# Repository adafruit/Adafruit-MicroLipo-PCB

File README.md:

# Adafruit MicroLipo and MiniLipo Charging Boards/Backpacks

&nbsp; 
<br />
&nbsp; 
<br />
&nbsp; 
<br />

Click to purchase from the Adafruit Shop:
- [Adafruit Micro-Lipo Charger for LiPo/LiIon Batt w/MicroUSB Jack - v1](https://www.adafruit.com/product/1904)
- [Adafruit Micro Lipo - USB LiIon/LiPoly charger - v1](https://www.adafruit.com/product/1304)
- [Adafruit Mini Lipo w/Mini-B USB Jack - USB LiIon/LiPoly charger - v1](https://www.adafruit.com/product/1905)
- [Adafruit LiIon/LiPoly Backpack Add-On for Pro Trinket/ItsyBitsy](https://www.adafruit.com/product/2124)
- [Adafruit Micro-Lipo Charger for LiPoly Batt with USB Type C Jack](https://www.adafruit.com/product/4410)
- [Adafruit Micro Lipo - USB LiIon/LiPoly charger - v2](https://www.adafruit.com/product/1304)

Oh so handy, this little lipo charger is so small and easy to use you can keep it on your desk or mount it easily into any project! Simply plug it via any MicroUSB cable into a USB port and a 3.7V/4.2V lithium polymer or lithium ion rechargeable battery into the JST plug on the other end. There are two LEDs - one red and one green. While charging, the red LED is lit. When the battery is fully charged and ready for use, the green LED turns on. Seriously, it could not get more easy.

These are the PCB files for the Adafruit Mini/MicroLipo battery chargers. The 
Format is EagleCAD schematic and board layout.

### License

Adafruit invests time and resources providing this open source design, please support Adafruit and open-source hardware by purchasing products from [Adafruit](https://www.adafruit.com)!

All text above must be included in any redistribution

Designed by Limor Fried/Ladyada for Adafruit Industries.
Creative Commons Attribution/Share-Alike, all text above must be included in any redistribution. 
See license.txt for additional information.

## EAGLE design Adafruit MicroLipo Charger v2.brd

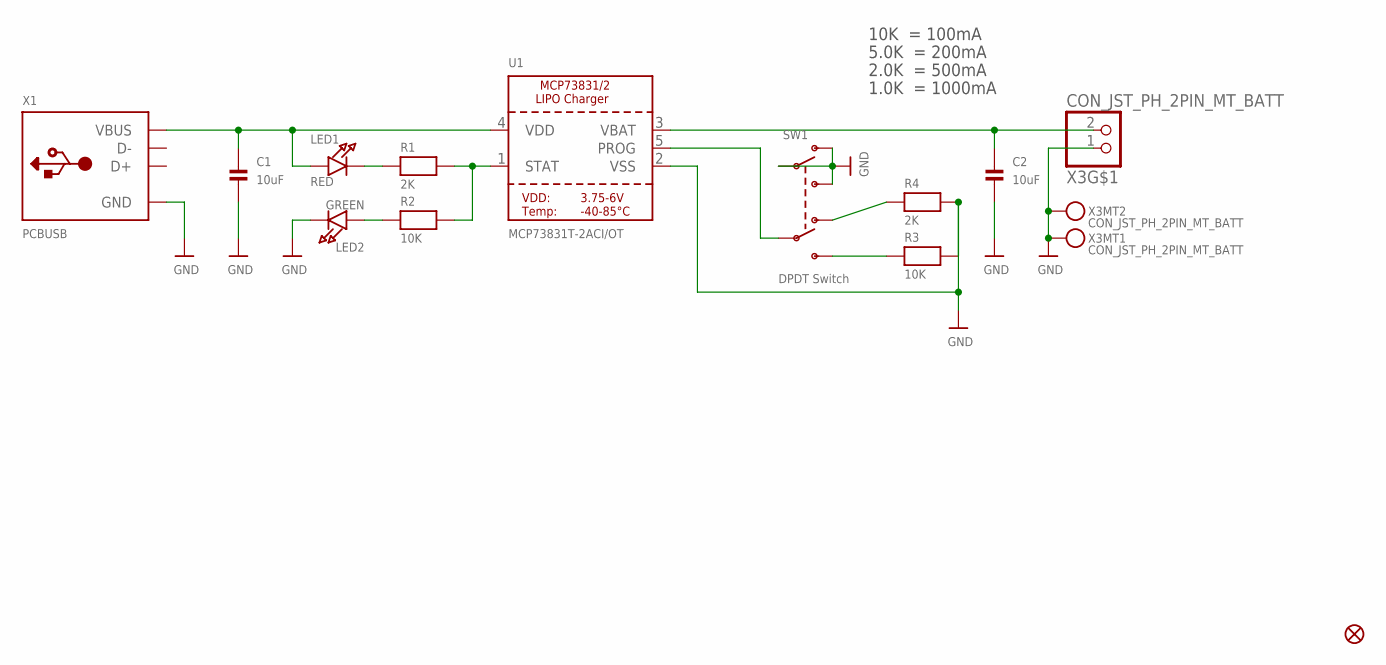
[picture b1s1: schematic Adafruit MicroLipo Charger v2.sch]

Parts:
C1, C2: 10uF; 0805-NO
FID1: FIDUCIAL_1MM
LED1: RED; CHIPLED_0603_NOOUTLINE
LED2: GREEN; CHIPLED_0603_NOOUTLINE
R1, R4: 2K; 0603-NO
R2, R3: 10K; 0603-NO
SW1: DPDT Switch; EG1390
U1: MCP73831T-2ACI/OT; SOT23-5
X1: PCBUSB; USBA_PCB
X3: CON_JST_PH_2PIN_MT_BATT; JSTPH2_BATT

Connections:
GND: C1.2, C2.2, LED2.C, R3.2, R4.2, SW1.O1, SW1.P1, SW1.S1, U1.2 (VSS), X1.GND, X3.1, X3.NC1, X3.NC2
unnamed: LED1.C, R1.1
unnamed: R1.2, R2.2, U1.1 (STAT)
unnamed: R3.1, SW1.S2
unnamed: R4.1, SW1.O2
unnamed: SW1.P2, U1.5 (PROG)
unnamed: LED2.A, R2.1
VBAT: C2.1, U1.3 (VBAT), X3.2
VDD: C1.1, LED1.A, U1.4 (VDD), X1.VCC (VBUS)

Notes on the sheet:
10K = 100mA
5.0K = 200mA
2.0K = 500mA
1.0K = 1000mA

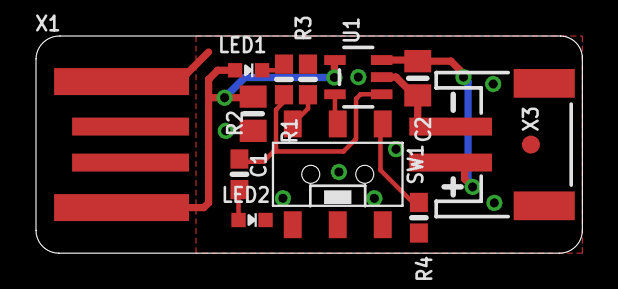
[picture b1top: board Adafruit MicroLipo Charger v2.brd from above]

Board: 2 copper layers, 30.4 x 12.1 mm, 27 parts (5 on the bottom side), 9 nets.

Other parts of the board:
PLABEL0: PLABEL0
PLABEL1: PLABEL1
PLABEL2: PLABEL2
PLABEL3: PLABEL3
PLABEL4: PLABEL4
PLABEL5: PLABEL5
PLABEL6: PLABEL6
PLABEL7: PLABEL7
PLABEL8: PLABEL8
PLABEL9: PLABEL9
PLABEL10: PLABEL10
PLABEL11: PLABEL11
U$8: ADAFRUIT_TEXT_20MM
U$9: PCBFEAT-REV-040

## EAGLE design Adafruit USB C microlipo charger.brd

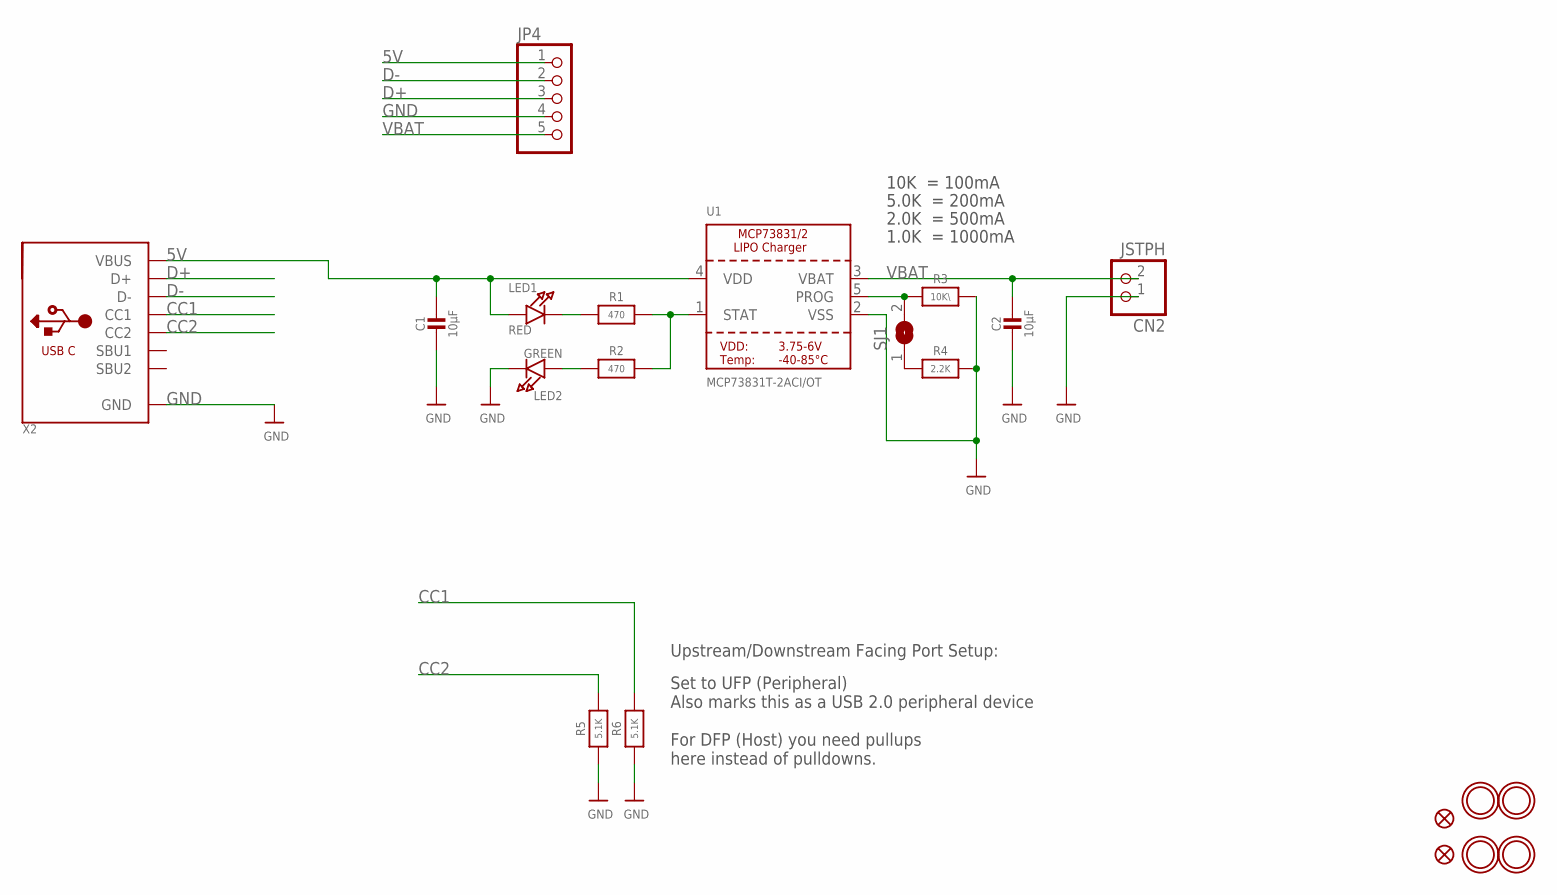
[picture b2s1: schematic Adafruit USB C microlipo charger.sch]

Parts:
C1, C2: 10µF; 0805-NO@1
CN2: JSTPH; JSTPH2
FID1, FID2: FIDUCIAL""; FIDUCIAL_1MM
JP4: HEADER-1X570MIL; 1X05_ROUND_70
LED1: RED; CHIPLED_0805_NOOUTLINE
LED2: GREEN; CHIPLED_0805_NOOUTLINE
R1, R2: 470; 0603-NO
R3: 10K\; 0603-NO
R4: 2.2K; 0603-NO
R5, R6: 5.1K; 0603-NO
SJ1: SOLDERJUMPER; SOLDERJUMPER_ARROW_NOPASTE
U1: MCP73831T-2ACI/OT; SOT23-5
U$9, U$10, U$11, U$12: MOUNTINGHOLE2.5; MOUNTINGHOLE_2.5_PLATED
X2: USB_C; USB_C_CUSB31-CFM2AX-01-X

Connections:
5V: C1.1, JP4.1, LED1.A, U1.4 (VDD), X2.A4B9 (VBUS), X2.B4A9 (VBUS)
CC1: R6.2, X2.A5 (CC1)
CC2: R5.2, X2.B5 (CC2)
D+: JP4.3, X2.A6 (D+), X2.B6 (D+)
D-: JP4.2, X2.A7 (D-), X2.B7 (D-)
GND: C1.2, C2.2, CN2.1, JP4.4, LED2.C, R3.2, R4.2, R5.1, R6.1, U1.2 (VSS), X2.A1B12 (GND), X2.B1A12 (GND)
unnamed: LED1.C, R1.1
unnamed: R1.2, R2.2, U1.1 (STAT)
unnamed: R4.1, SJ1.1
unnamed: R3.1, SJ1.2, U1.5 (PROG)
unnamed: LED2.A, R2.1
VBAT: C2.1, CN2.2, JP4.5, U1.3 (VBAT)

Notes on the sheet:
10K = 100mA
5.0K = 200mA
2.0K = 500mA
1.0K = 1000mA
Set to UFP (Peripheral) Also marks this as a USB 2.0 peripheral device For DFP (Host) you need pullups here instead of pulldowns.
Upstream/Downstream Facing Port Setup:

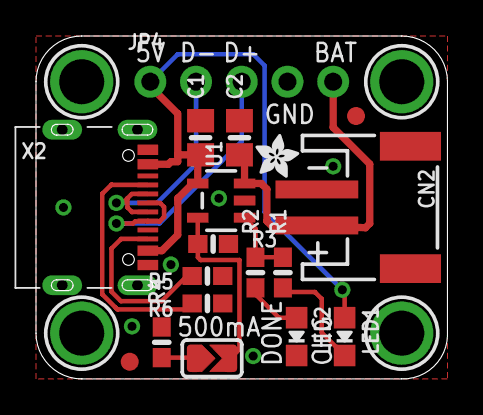
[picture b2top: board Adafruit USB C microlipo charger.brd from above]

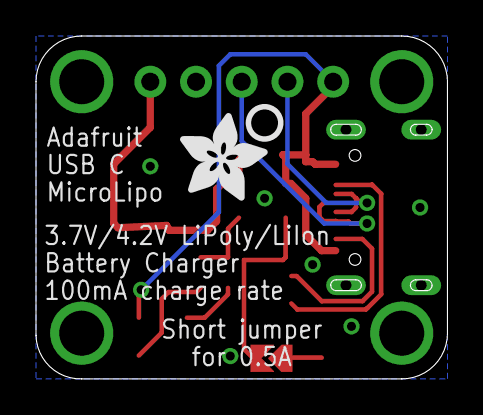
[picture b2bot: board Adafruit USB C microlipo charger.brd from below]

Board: 2 copper layers, 22.9 x 19.1 mm, 24 parts (2 on the bottom side), 12 nets.

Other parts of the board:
U$2: ADAFRUIT_2.5MM
U$13: ADAFRUIT_5MM
U$16: PCBFEAT-REV-040

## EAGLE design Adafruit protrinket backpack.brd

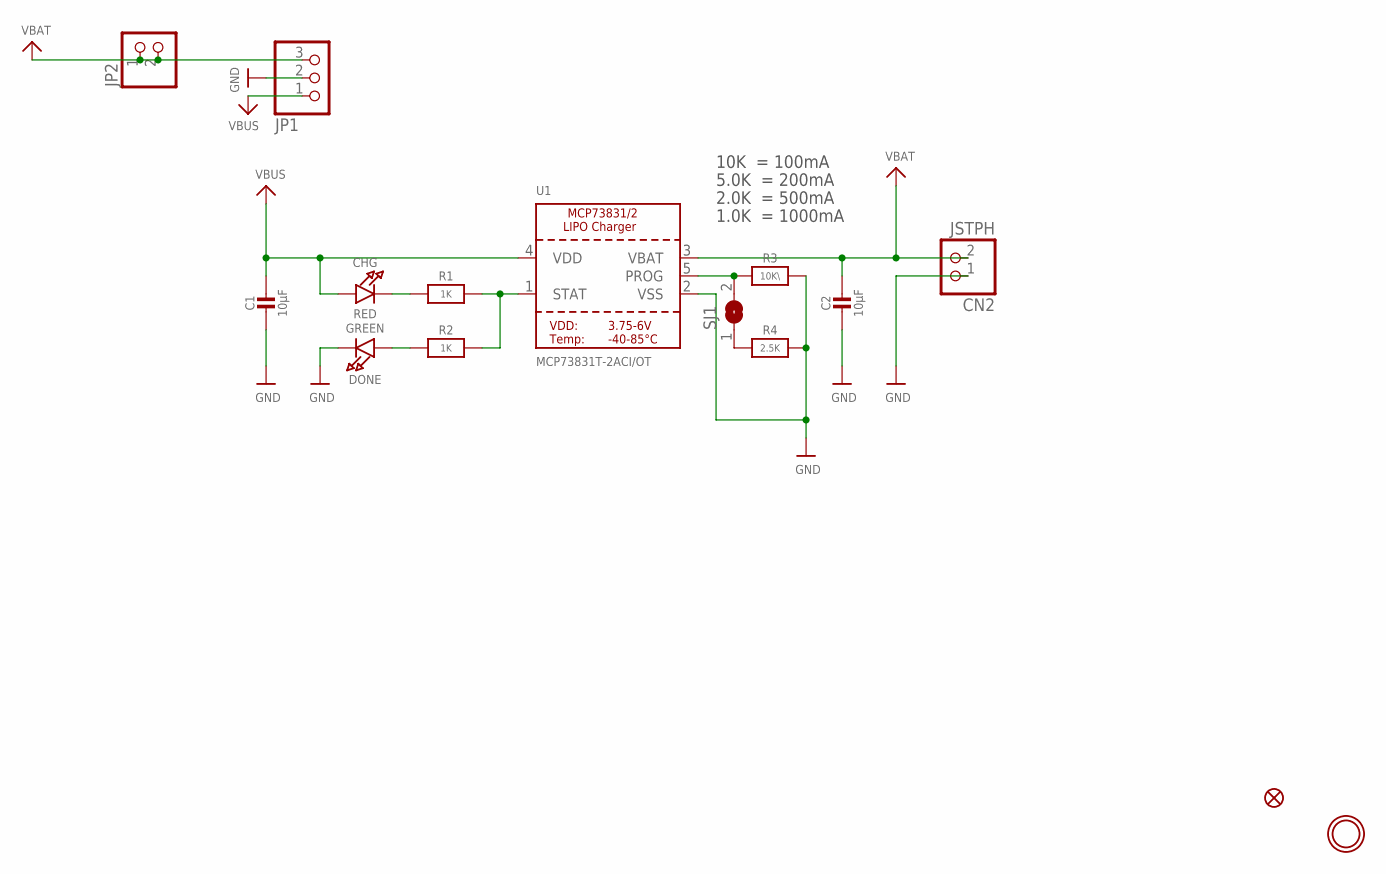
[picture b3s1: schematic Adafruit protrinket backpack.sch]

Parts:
C1, C2: 10µF; 0805-NO
CHG: RED; CHIPLED_0805_NOOUTLINE
CN2: JSTPH; JSTPH2
DONE: GREEN; CHIPLED_0805_NOOUTLINE
FID1: FIDUCIAL""; FIDUCIAL_1MM
JP1: HEADER-1X376MIL; 1X03_ROUND_76
JP2: HEADER-1X2ROUND; 1X02_ROUND
R1, R2: 1K; 0805-NO
R3: 10K\; _0805MP
R4: 2.5K; 0805-NO
SJ1: SOLDERJUMPER; SOLDERJUMPER_ARROW_NOPASTE
U1: MCP73831T-2ACI/OT; SOT23-5
U$10: MOUNTINGHOLE2.5; MOUNTINGHOLE_2.5_PLATED

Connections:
GND: C1.2, C2.2, CN2.1, DONE.C, JP1.2, R3.2, R4.2, U1.2 (VSS)
unnamed: CHG.C, R1.1
unnamed: R1.2, R2.2, U1.1 (STAT)
unnamed: R4.1, SJ1.1
unnamed: R3.1, SJ1.2, U1.5 (PROG)
unnamed: DONE.A, R2.1
VBAT: C2.1, CN2.2, JP1.3, JP2.1, JP2.2, U1.3 (VBAT)
VBUS: C1.1, CHG.A, JP1.1, U1.4 (VDD)

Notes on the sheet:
10K = 100mA
5.0K = 200mA
2.0K = 500mA
1.0K = 1000mA

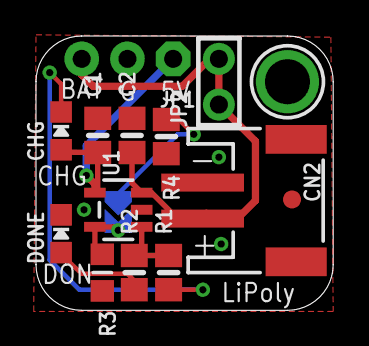
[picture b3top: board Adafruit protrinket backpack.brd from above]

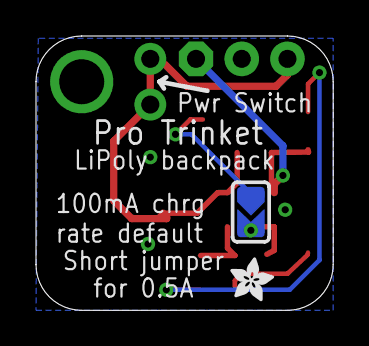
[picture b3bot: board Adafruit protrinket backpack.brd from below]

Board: 2 copper layers, 16.5 x 15.2 mm, 16 parts (2 on the bottom side), 8 nets.

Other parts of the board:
U$9: ADAFRUIT_2.5MM

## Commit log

2014-01-09 init
2014-01-09 read
2014-07-22 new revs with usb!
2014-12-10 added the pro trinket version
2019-11-05 Adding USB C image file
2019-11-05 Adding USBC
2022-11-10 adding v2 microlipo
2022-11-10 fixing formatting
2022-11-10 moving link

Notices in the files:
parts and their libraries:
microbuilder: This work is placed in the public domain, and may be freely used for commercial and non-commercial work with the following conditions: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
